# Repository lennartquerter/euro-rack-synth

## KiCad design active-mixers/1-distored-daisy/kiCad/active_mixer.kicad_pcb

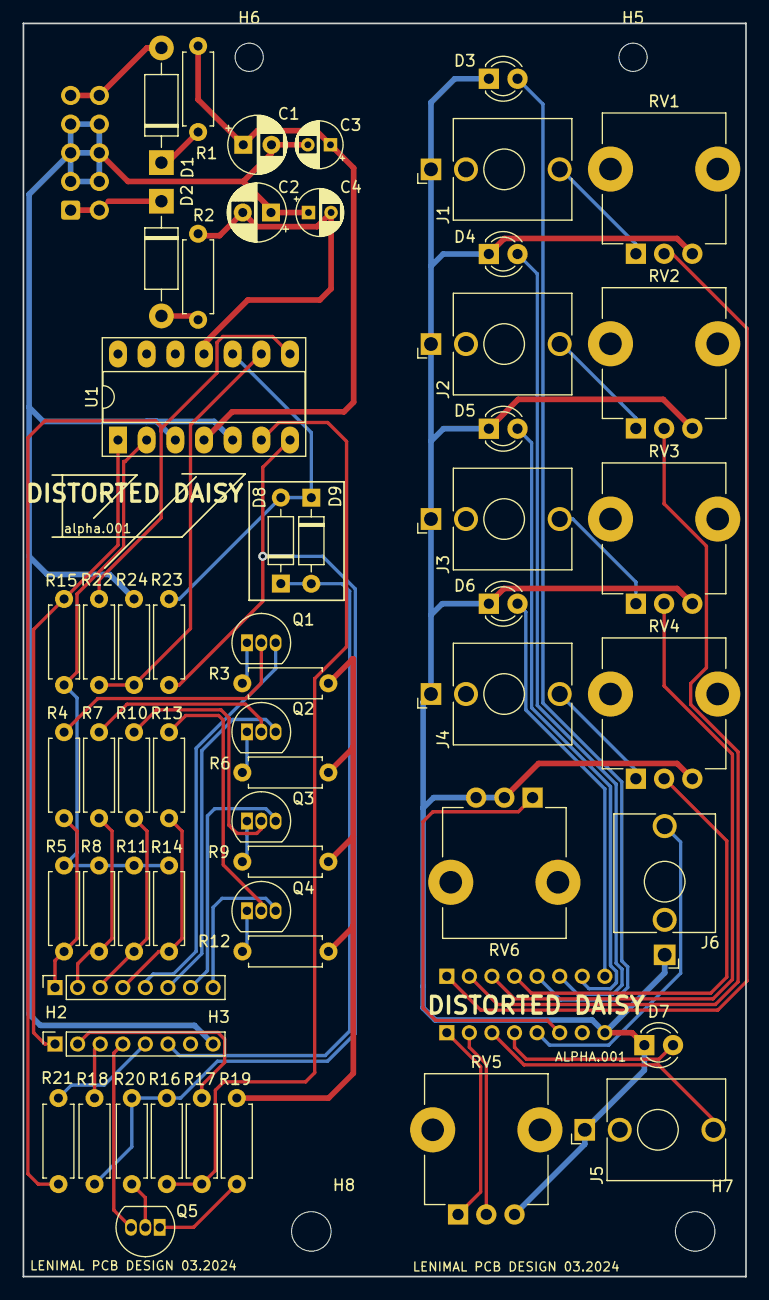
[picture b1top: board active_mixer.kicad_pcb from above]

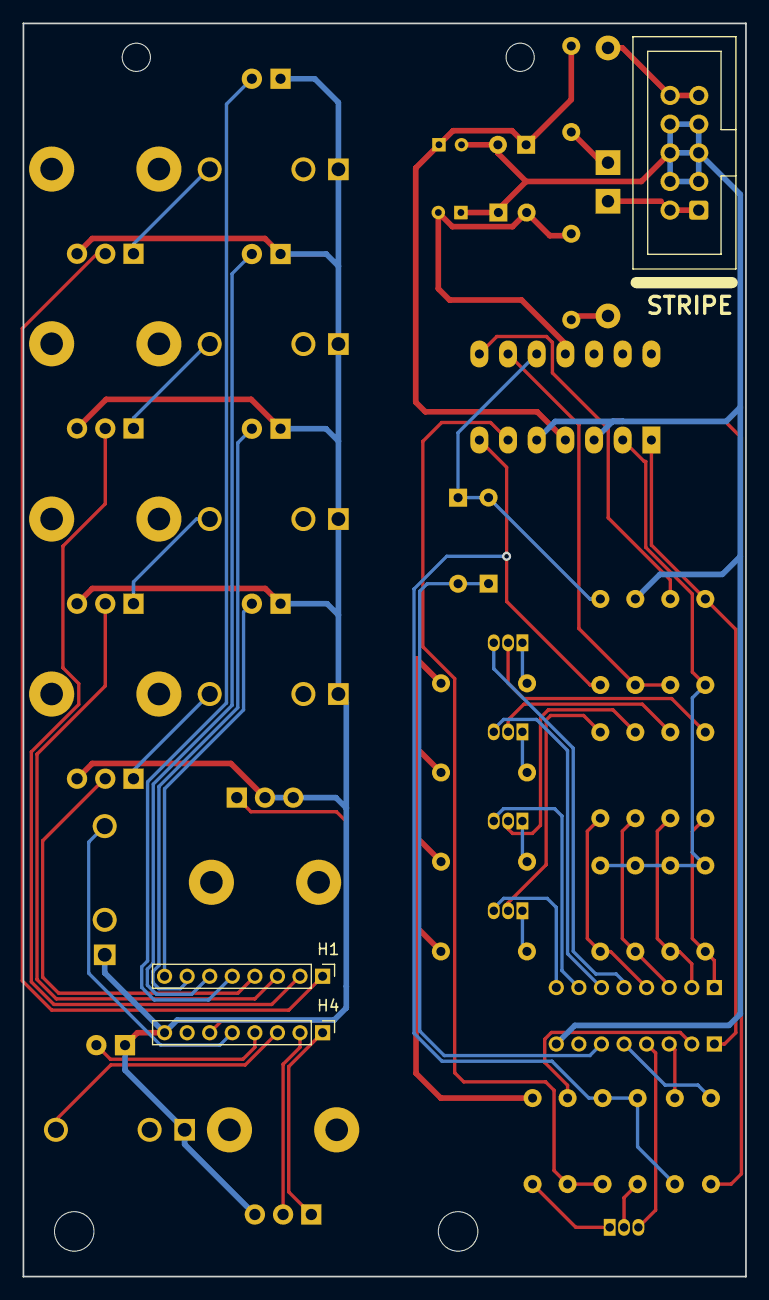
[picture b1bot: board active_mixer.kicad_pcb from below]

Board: 2 copper layers, 64.0 x 111.0 mm, 64 parts (3 on the bottom side), 55 nets.

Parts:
C1, C2: 47uF; CP_Radial_D5.0mm_P2.50mm
C3, C4: 0.1uF; CP_Radial_D4.0mm_P2.00mm
D1, D2: 1N5819; D_DO-41_SOD81_P10.16mm_Horizontal
D3: LED_IN_1; LED_D3.0mm
D4: LED_IN_2; LED_D3.0mm
D5: LED_IN_3; LED_D3.0mm
D6: LED_IN_4; LED_D3.0mm
D7: LED_OUT; LED_D3.0mm
D8, D9: 1N4148; D_DO-35_SOD27_P7.62mm_Horizontal
H1, H4: PinHeader_1x08_P2.00mm_Vertical
H2, H3: PinSocket_1x08_P2.00mm_Vertical
H5, H6: MountingHole; MountingHole_2.5mm
H7, H8: MountingHole; MountingHole_3.5mm
H9: Conn_02x05_PWR_Eurorack; CONN_02x05_PWR
J1: INPUT_1; Jack_3.5mm_QingPu_WQP-PJ398SM_Vertical_CircularHoles
J2: INPUT_2; Jack_3.5mm_QingPu_WQP-PJ398SM_Vertical_CircularHoles
J3: INPUT_3; Jack_3.5mm_QingPu_WQP-PJ398SM_Vertical_CircularHoles
J4: INPUT_4; Jack_3.5mm_QingPu_WQP-PJ398SM_Vertical_CircularHoles
J5, J6: OUTPUT; Jack_3.5mm_QingPu_WQP-PJ398SM_Vertical_CircularHoles
Q1, Q2, Q3, Q4, Q5: BC547; TO-92_Inline
R1, R2: 10; R_Axial_DIN0207_L6.3mm_D2.5mm_P7.62mm_Horizontal
R3, R6, R9, R12, R18, R19, R21: 1K; R_Axial_DIN0207_L6.3mm_D2.5mm_P7.62mm_Horizontal
R4, R5, R7, R8, R10, R11, R13, R14, R15, R16, R17, R20, R22, R24: 100K; R_Axial_DIN0207_L6.3mm_D2.5mm_P7.62mm_Horizontal
R23: 27K; R_Axial_DIN0207_L6.3mm_D2.5mm_P7.62mm_Horizontal
RV1, RV2, RV3, RV4, RV5: B100K; Potentiometer_TT_P0915N
RV6: B20K; Potentiometer_TT_P0915N
U1: TL074; DIP-14_W7.62mm_Socket_LongPads

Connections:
+12V: C1.1, C3.1, R1.2, R3.1, R6.1, R9.1, R12.1, R19.1, U1.4 (V+)
-12V: C2.2, C4.2, R2.2, U1.11 (V-)
GNDREF: C1.2, C2.1, C3.2, C4.1, D3.1 (K), D4.1 (K), D5.1 (K), D6.1 (K), D7.1 (K), H3.8, H4.8, H9.3, H9.4, H9.5, H9.6, H9.7, H9.8, J1.S, J2.S, J3.S, J4.S, J5.S, J6.S, R23.1, RV1.3, RV2.3, RV3.3, RV4.3, RV5.3, RV6.2, RV6.3, U1.3 (+), U1.5 (+)
unnamed: D1.2 (A), H9.9, H9.10
unnamed: D1.1 (K), R1.1
unnamed: D2.2 (A), R2.1
unnamed: D2.1 (K), H9.1, H9.2
unnamed: D3.2 (A), H1.5
unnamed: D4.2 (A), H1.6
unnamed: D5.2 (A), H1.7
unnamed: D6.2 (A), H1.8
unnamed: D7.2 (A), H4.4
unnamed: D8.2 (A), D9.1 (K), R24.2, U1.10 (+)
unnamed: D8.1 (K), D9.2 (A), H3.6
unnamed: H1.1, RV1.2
unnamed: H1.2, RV2.2
unnamed: H1.3, RV3.2
unnamed: H1.4, RV4.2
unnamed: H2.1, R4.1, R5.1
unnamed: H2.2, R7.1, R8.1
unnamed: H2.3, R10.1, R11.1
unnamed: H2.4, R13.1, R14.1
unnamed: H3.1, R15.2, U1.1
unnamed: H3.2, R17.1
unnamed: H3.3, R18.2
unnamed: H3.5, R21.2
unnamed: H4.1, RV5.1
unnamed: H4.2, RV5.2
unnamed: H4.3, J5.T
unnamed: H4.5, J6.T
unnamed: H4.6, RV6.1
unnamed: J1.T, RV1.1
unnamed: J2.T, RV2.1
unnamed: J3.T, RV3.1
unnamed: J4.T, RV4.1
unnamed: Q1.2 (B), R4.2
unnamed: Q1.1 (C), R3.2
unnamed: H2.5, Q1.3 (E)
unnamed: Q2.2 (B), R7.2
unnamed: Q2.1 (C), R6.2
unnamed: H2.6, Q2.3 (E)
unnamed: Q3.2 (B), R10.2
unnamed: Q3.1 (C), R9.2
unnamed: H2.7, Q3.3 (E)
unnamed: Q4.2 (B), R13.2
unnamed: Q4.1 (C), R12.2
unnamed: H2.8, Q4.3 (E)
unnamed: Q5.2 (B), R20.2
unnamed: Q5.1 (C), R19.2
unnamed: H3.4, Q5.3 (E)
unnamed: R16.2, R18.1, R20.1, R24.1, U1.7
unnamed: R21.1, R22.2, U1.8
unnamed: R5.2, R8.2, R11.2, R14.2, R15.1, U1.2 (-)
unnamed: R16.1, R17.2, U1.6 (-)
unnamed: R22.1, R23.2, U1.9 (-)

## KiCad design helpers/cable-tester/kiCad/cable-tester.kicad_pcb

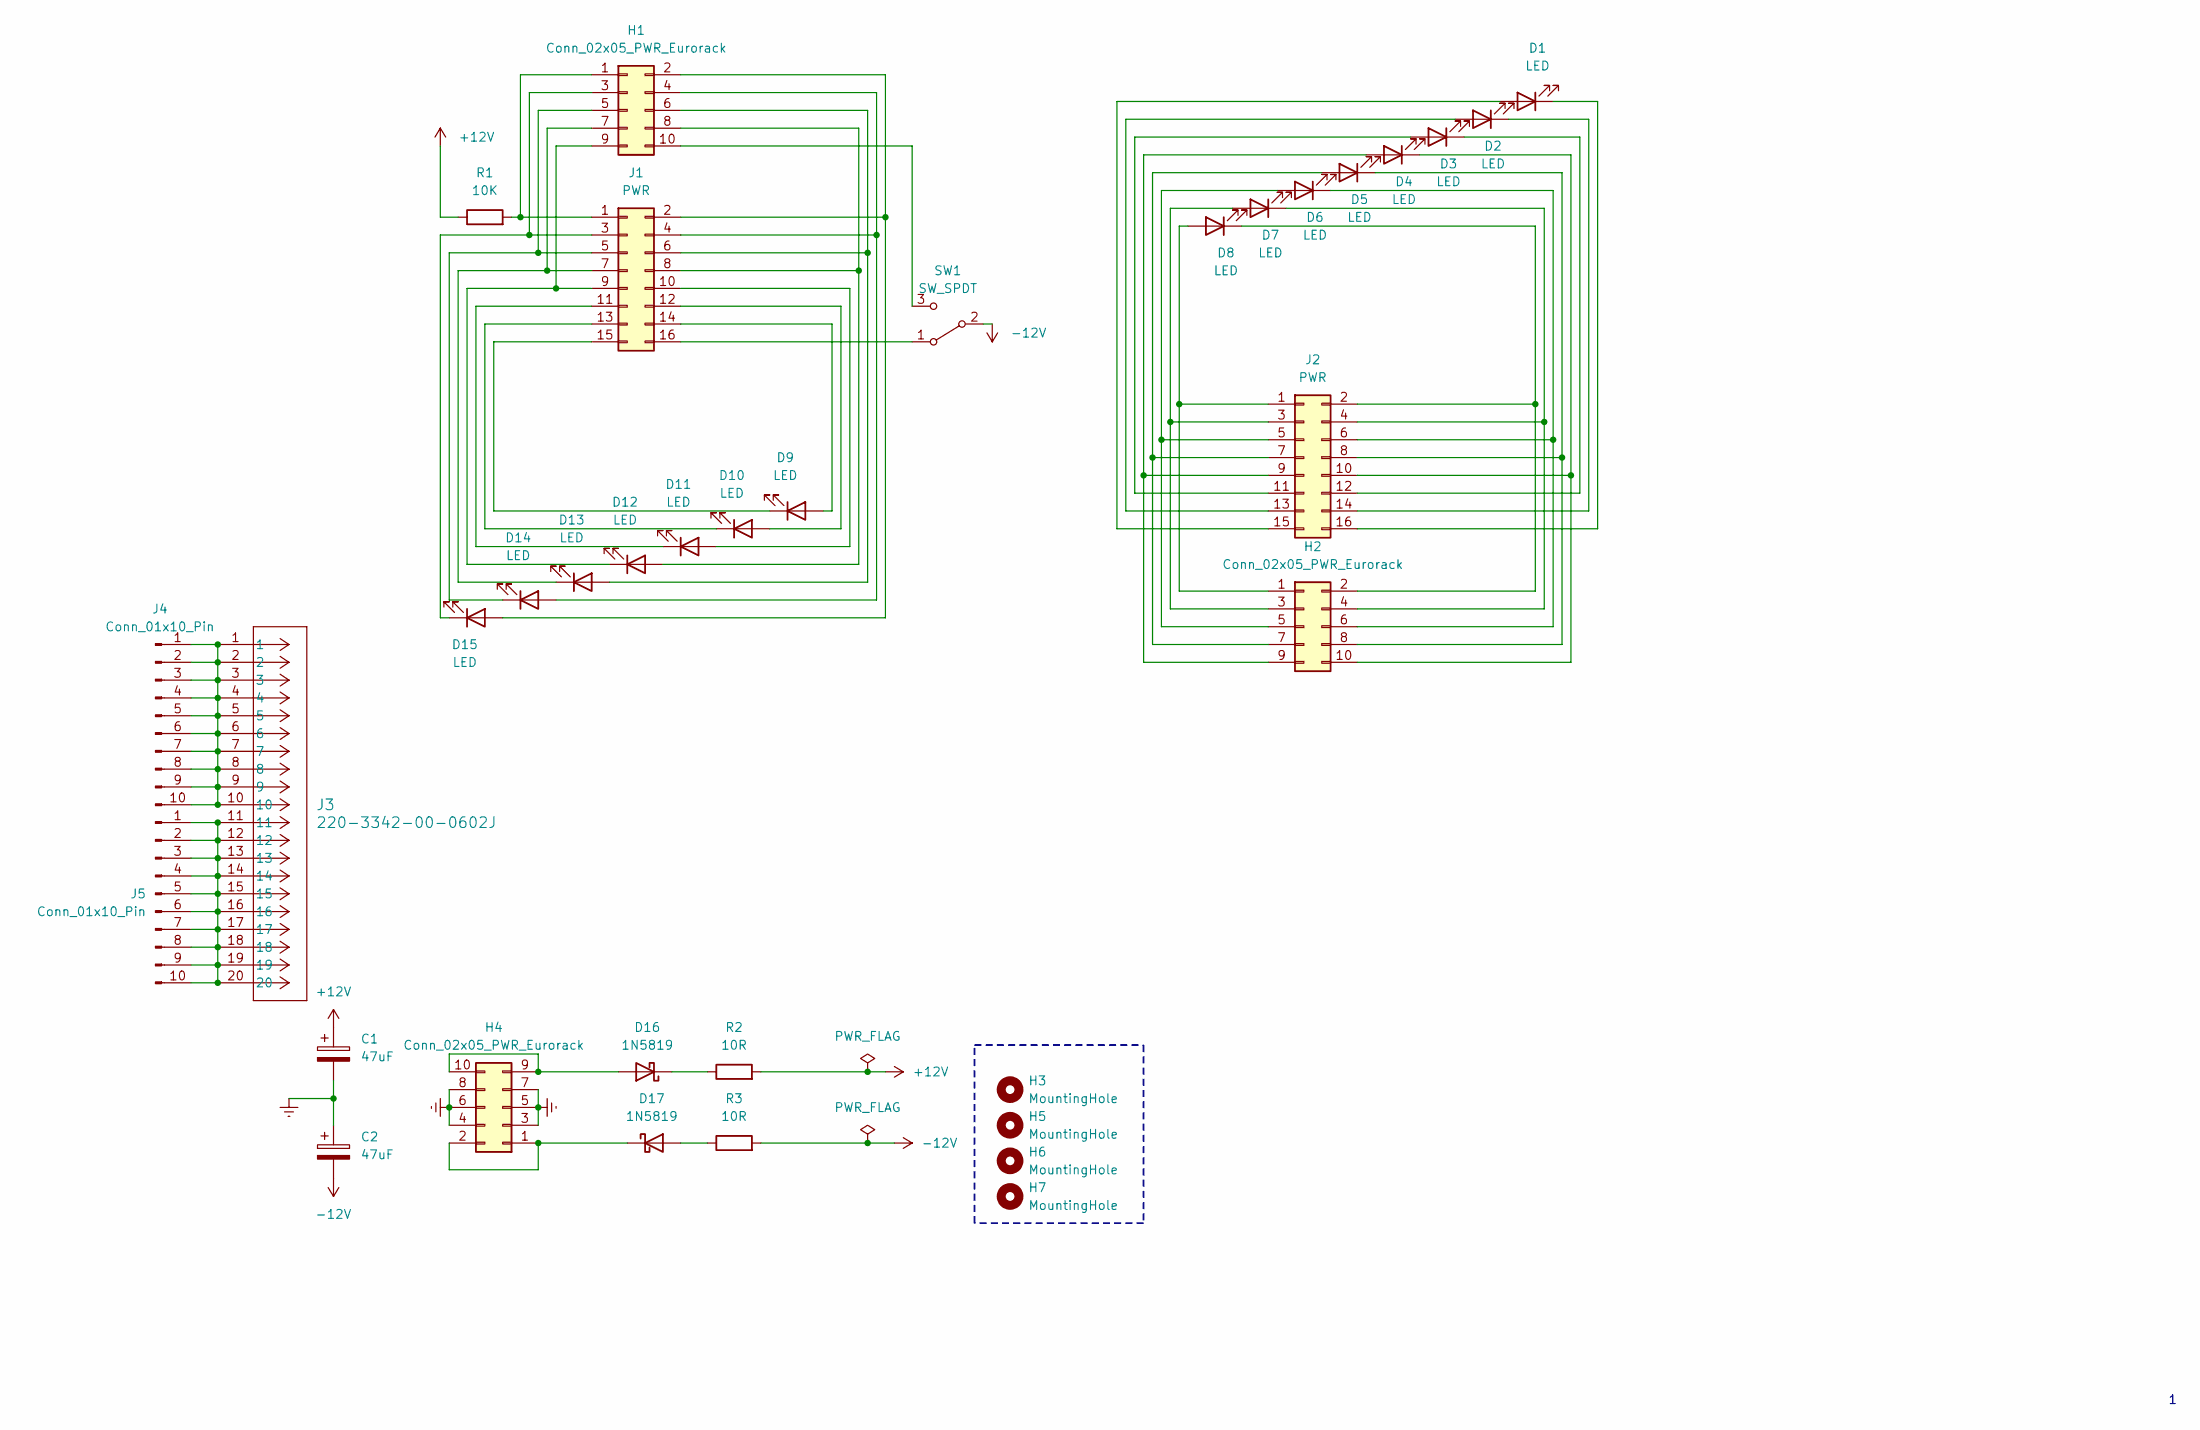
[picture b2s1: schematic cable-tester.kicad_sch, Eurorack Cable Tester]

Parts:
C1, C2: 47uF; CP_Radial_D6.3mm_P2.50mm
D1, D2, D3, D4, D5, D6, D7, D8, D9, D10, D11, D12, D13, D14, D15: LED; LED_D3.0mm
D16, D17: 1N5819; D_SOD-123
H1, H2, H4: Conn_02x05_PWR_Eurorack; IDC-Header_2x05_P2.54mm_Vertical
H3, H5, H6, H7: MountingHole; MountingHole_3.2mm_M3
J1, J2: PWR; IDC-Header_2x08_P2.54mm_Vertical
J3: 220-3342-00-0602J; DIP_tester_20pos
J4, J5: Conn_01x10_Pin; PinHeader_1x10_P2.54mm_Vertical
R1: 10K; R_0805_2012Metric_Pad1.20x1.40mm_HandSolder
R2, R3: 10R; R_0805_2012Metric_Pad1.20x1.40mm_HandSolder
SW1: SW_SPDT; SW_default

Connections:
+12V: C1.1, R1.1, R2.2
-12V: C2.2, R3.2, SW1.2 (B)
GNDREF: C1.2, C2.1, H4.3, H4.4, H4.5, H4.6, H4.7, H4.8
unnamed: D1.2 (A), J2.15 (GATE)
unnamed: D1.1 (K), J2.16 (GATE)
unnamed: D2.2 (A), J2.13 (CV)
unnamed: D2.1 (K), J2.14 (CV)
unnamed: D3.2 (A), J2.11 (+5V)
unnamed: D3.1 (K), J2.12 (+5V)
unnamed: D4.2 (A), H2.9, J2.9 (+12V)
unnamed: D4.1 (K), H2.10, J2.10 (+12V)
unnamed: D5.2 (A), H2.7, J2.7 (GND)
unnamed: D5.1 (K), H2.8, J2.8 (GND)
unnamed: D6.2 (A), H2.5, J2.5 (GND)
unnamed: D6.1 (K), H2.6, J2.6 (GND)
unnamed: D7.2 (A), H2.3, J2.3 (GND)
unnamed: D7.1 (K), H2.4, J2.4 (GND)
unnamed: D8.2 (A), H2.1, J2.1 (-12V)
unnamed: D8.1 (K), H2.2, J2.2 (-12V)
unnamed: D9.2 (A), J1.14 (CV)
unnamed: D9.1 (K), J1.15 (GATE)
unnamed: D10.2 (A), J1.12 (+5V)
unnamed: D10.1 (K), J1.13 (CV)
unnamed: D11.2 (A), J1.10 (+12V)
unnamed: D11.1 (K), J1.11 (+5V)
unnamed: D12.2 (A), H1.8, J1.8 (GND)
unnamed: D12.1 (K), H1.9, J1.9 (+12V)
unnamed: D13.2 (A), H1.6, J1.6 (GND)
unnamed: D13.1 (K), H1.7, J1.7 (GND)
unnamed: D14.2 (A), H1.4, J1.4 (GND)
unnamed: D14.1 (K), H1.5, J1.5 (GND)
unnamed: D15.2 (A), H1.2, J1.2 (-12V)
unnamed: D15.1 (K), H1.3, J1.3 (GND)
unnamed: D16.2 (A), H4.9, H4.10
unnamed: D16.1 (K), R2.1
unnamed: D17.2 (A), R3.1
unnamed: D17.1 (K), H4.1, H4.2
unnamed: H1.1, J1.1 (-12V), R1.2
unnamed: H1.10, SW1.3 (C)
unnamed: J3.1, J3.2, J3.3, J3.4, J3.5, J3.6, J3.7, J3.8, J3.9, J3.10, J4.1, J4.2, J4.3, J4.4, J4.5, J4.6, J4.7, J4.8, J4.9, J4.10
unnamed: J3.11, J3.12, J3.13, J3.14, J3.15, J3.16, J3.17, J3.18, J3.19, J3.20, J5.1, J5.2, J5.3, J5.4, J5.5, J5.6, J5.7, J5.8, J5.9, J5.10
unnamed: J1.16 (GATE), SW1.1 (A)

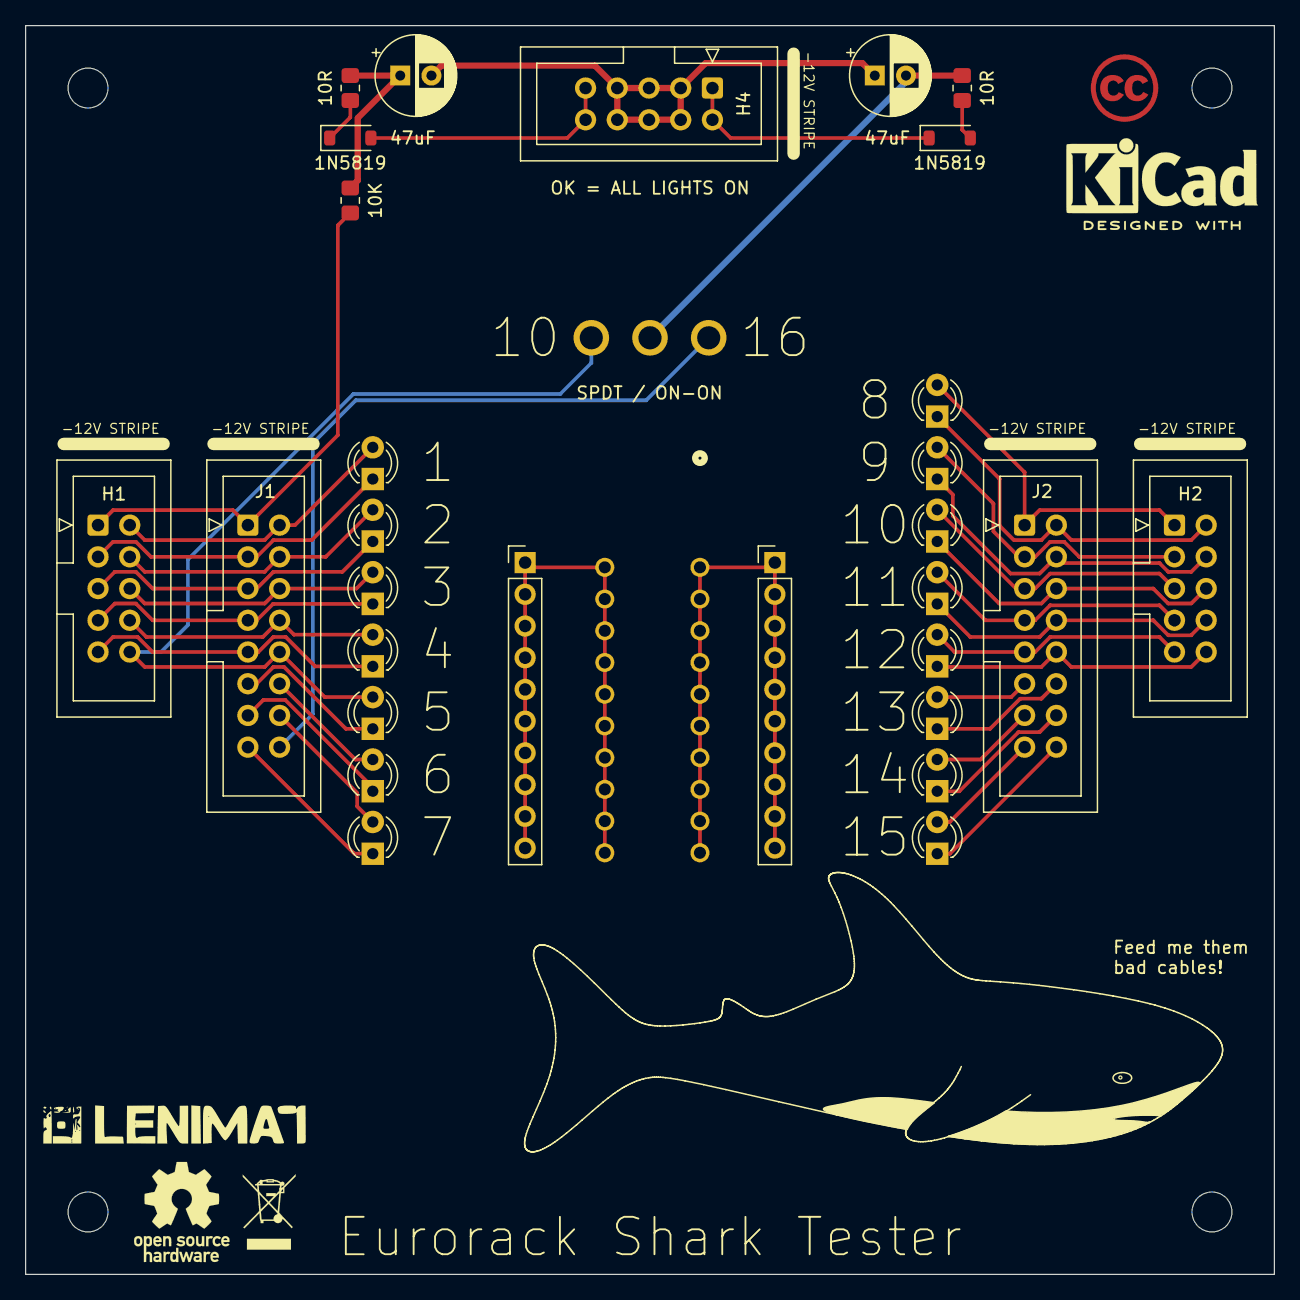
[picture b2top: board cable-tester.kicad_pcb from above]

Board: 2 copper layers, 100.0 x 100.0 mm, 35 parts (0 on the bottom side), 42 nets.

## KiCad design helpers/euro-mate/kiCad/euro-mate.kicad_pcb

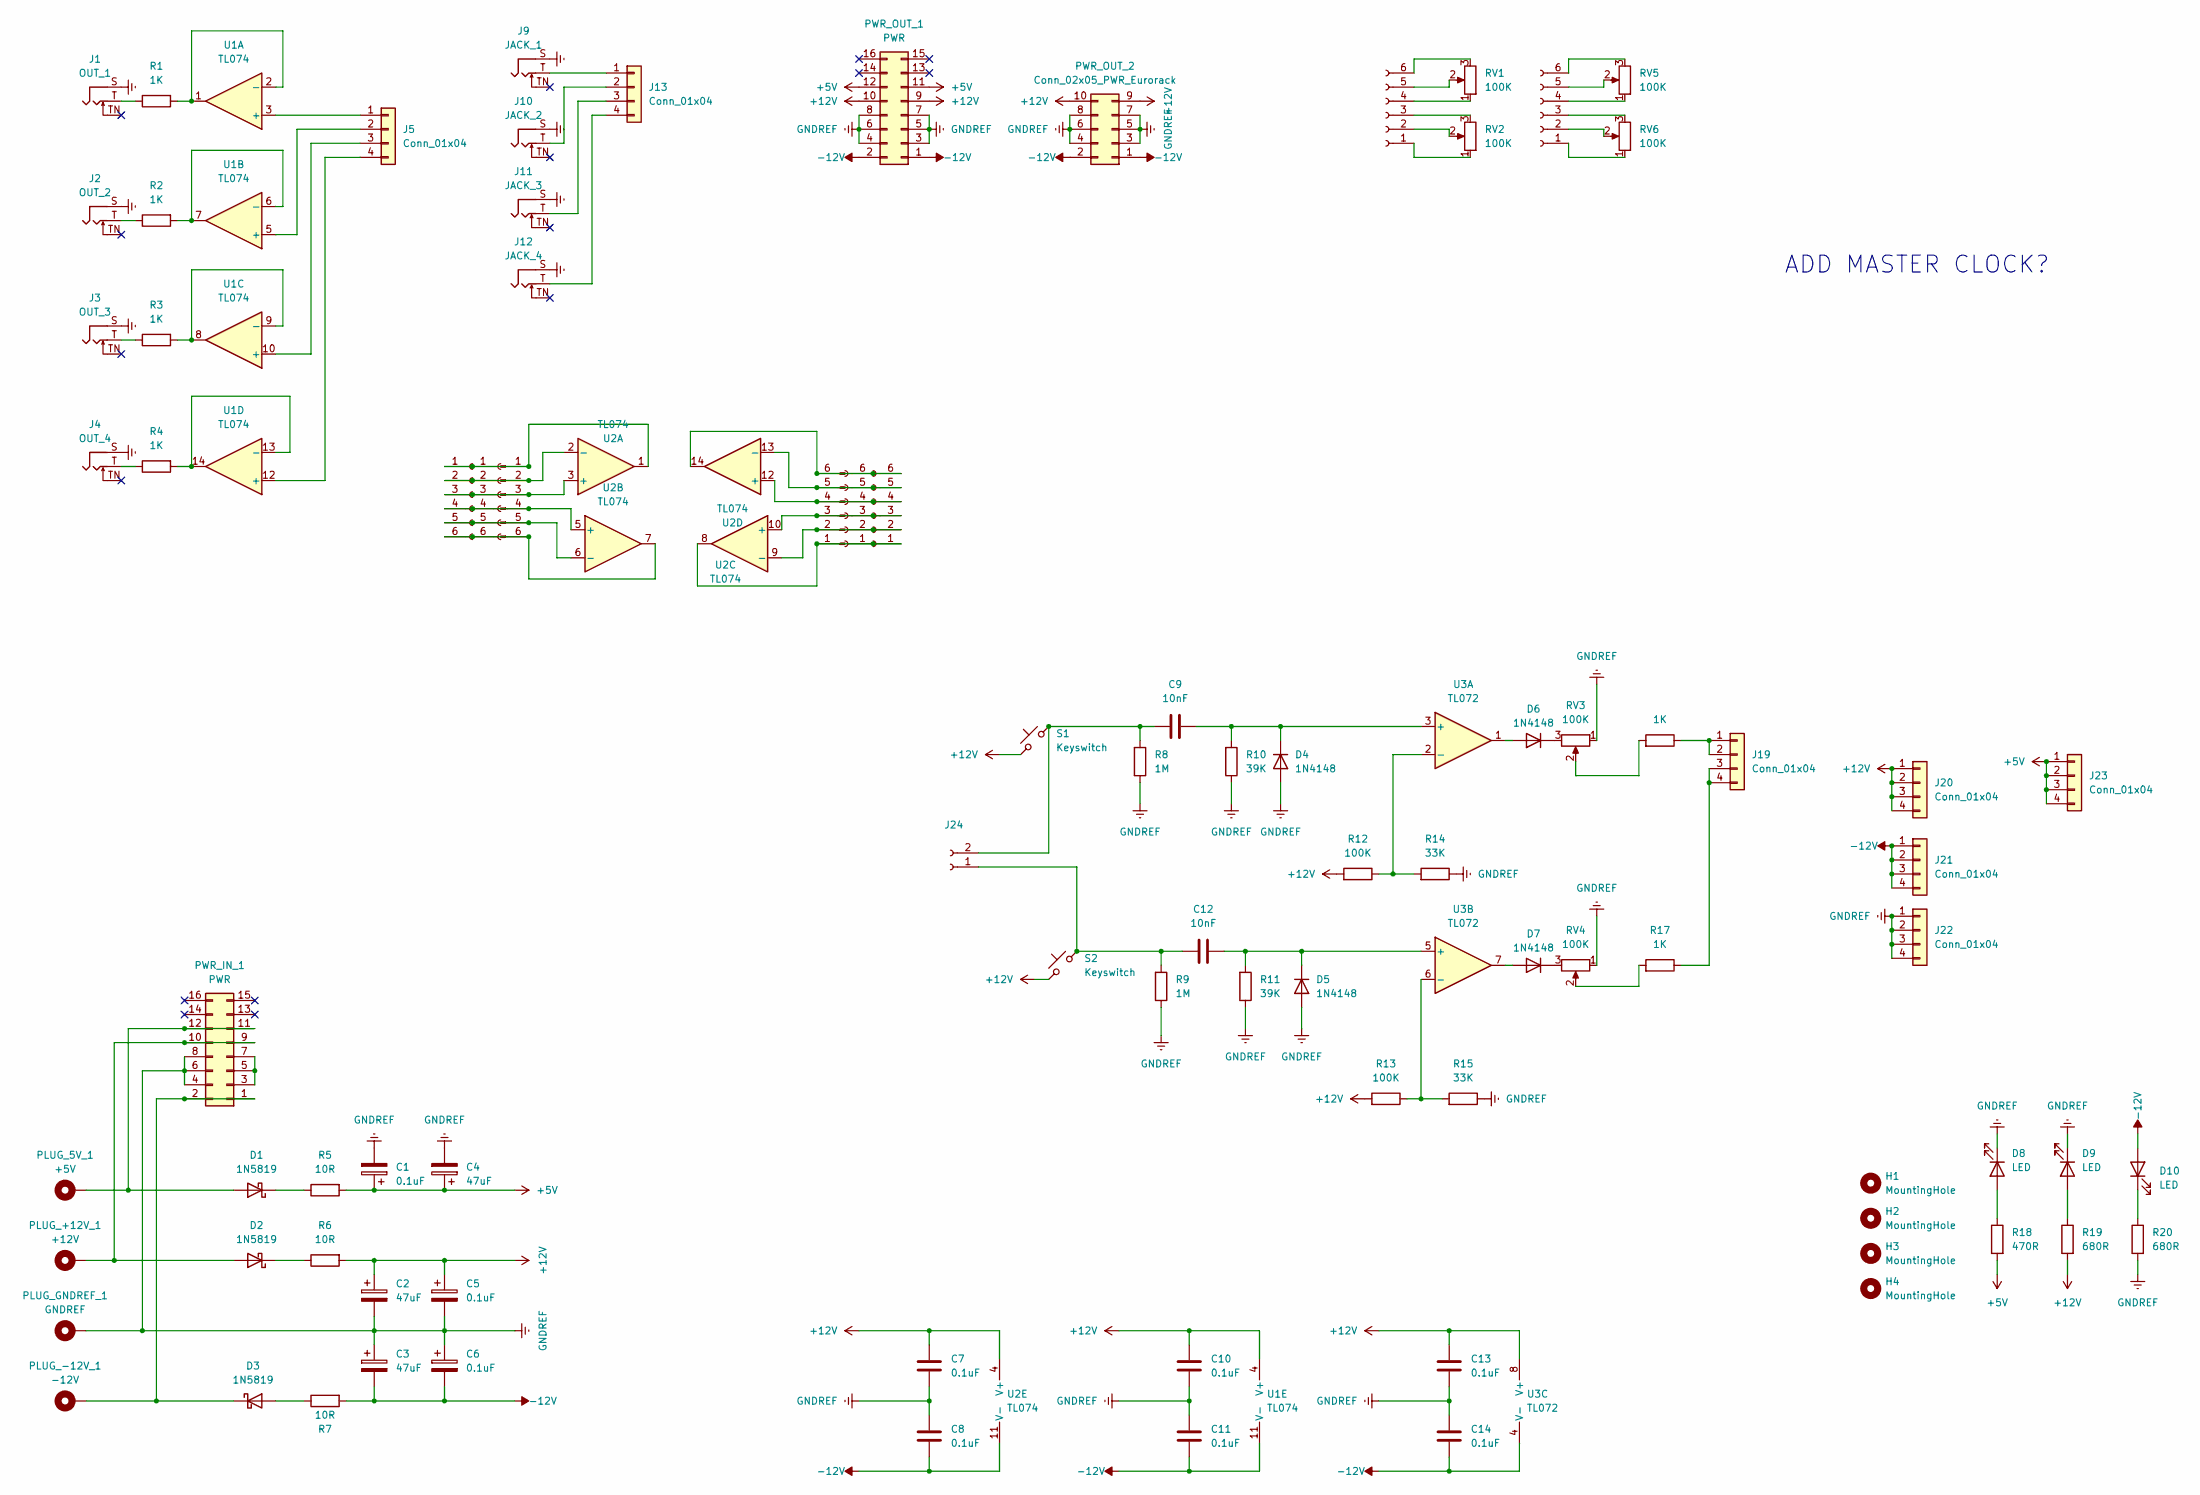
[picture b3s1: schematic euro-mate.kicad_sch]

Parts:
C1, C5, C6: 0.1uF; CP_Radial_D4.0mm_P2.00mm
C2, C3, C4: 47uF; CP_Radial_D6.3mm_P2.50mm
C7, C8, C10, C11, C13, C14: 0.1uF; C_RECT_WIMA_0.1uF
C9, C12: 10nF; C_RECT_WIMA_0.1uF
D1, D2, D3: 1N5819; D_DO-41_SOD81_P10.16mm_Horizontal
D4, D5, D6, D7: 1N4148; D_DO-35_SOD27_P7.62mm_Horizontal
D8, D9, D10: LED; LED_D5.0mm (center Aligned)
H1, H2, H3, H4: MountingHole; MountingHole_3.2mm_M3
J1: OUT_1; Jack_3.5mm_QingPu_WQP-PJ398SM_Vertical_CircularHoles
J2: OUT_2; Jack_3.5mm_QingPu_WQP-PJ398SM_Vertical_CircularHoles
J3: OUT_3; Jack_3.5mm_QingPu_WQP-PJ398SM_Vertical_CircularHoles
J4: OUT_4; Jack_3.5mm_QingPu_WQP-PJ398SM_Vertical_CircularHoles
J5, J13, J19, J20, J21, J22, J23: Conn_01x04; PinSocket_1x04_P2.54mm_Vertical
J6, J8, J15, J16, J17, J18: Conn_01x06_Socket; PinSocket_1x06_P2.54mm_Vertical
J7, J14: Conn_01x06_Pin; PinHeader_1x06_P2.54mm_Vertical
J9: JACK_1; Jack_3.5mm_QingPu_WQP-PJ398SM_Vertical_CircularHoles
J10: JACK_2; Jack_3.5mm_QingPu_WQP-PJ398SM_Vertical_CircularHoles
J11: JACK_3; Jack_3.5mm_QingPu_WQP-PJ398SM_Vertical_CircularHoles
J12: JACK_4; Jack_3.5mm_QingPu_WQP-PJ398SM_Vertical_CircularHoles
J24: Conn_01x02_Socket; PinSocket_1x02_P2.54mm_Vertical
PLUG_5V_1: +5V; MountingHole_4.3mm_M4_Pad
PLUG_+12V_1: +12V; MountingHole_4.3mm_M4_Pad
PLUG_-12V_1: -12V; MountingHole_4.3mm_M4_Pad
PLUG_GNDREF_1: GNDREF; MountingHole_4.3mm_M4_Pad
PWR_IN_1: PWR; IDC-Header_2x08_P2.54mm_Vertical
PWR_OUT_1: PWR; IDC-Header_2x08_P2.54mm_Vertical
PWR_OUT_2: Conn_02x05_PWR_Eurorack; IDC-Header_2x05_P2.54mm_Vertical
R1, R2, R3, R4, R16, R17: 1K; R_Default (DIN0207)
R5, R6, R7: 10R; R_Default (DIN0207)
R8, R9: 1M; R_Default (DIN0207)
R10, R11: 39K; R_Default (DIN0207)
R12, R13: 100K; R_Default (DIN0207)
R14, R15: 33K; R_Default (DIN0207)
R18: 470R; R_Default (DIN0207)
R19, R20: 680R; R_Default (DIN0207)
RV1, RV2, RV3, RV4, RV5, RV6: 100K; Potentiometer_TT_P0915N
S1, S2: Keyswitch; SW_Cherry_MX_PCB_1.00u
U1, U2: TL074; DIP-14_W7.62mm_Socket_LongPads
U3: TL072; DIP-8_W7.62mm_Socket_LongPads

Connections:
+5V: C1.1, C4.1, J23.1, J23.2, J23.3, J23.4, PWR_OUT_1.11 (+5V), PWR_OUT_1.12 (+5V), R5.1, R18.1
+12V: C2.1, C5.1, C7.1, C10.1, C13.1, J20.1, J20.2, J20.3, J20.4, PWR_OUT_1.9 (+12V), PWR_OUT_1.10 (+12V), PWR_OUT_2.9, PWR_OUT_2.10, R6.1, R12.1, R13.1, R19.1, S1.1, S2.1, U1.4 (V+), U2.4 (V+), U3.8 (V+)
-12V: C3.2, C6.2, C8.2, C11.2, C14.2, D10.2 (A), J21.1, J21.2, J21.3, J21.4, PWR_OUT_1.1 (-12V), PWR_OUT_1.2 (-12V), PWR_OUT_2.1, PWR_OUT_2.2, R7.1, U1.11 (V-), U2.11 (V-), U3.4 (V-)
GNDREF: C1.2, C2.2, C3.1, C4.2, C5.2, C6.1, C7.2, C8.1, C10.2, C11.1, C13.2, C14.1, D4.2 (A), D5.2 (A), D8.1 (K), D9.1 (K), J1.S, J2.S, J3.S, J4.S, J9.S, J10.S, J11.S, J12.S, J22.1, J22.2, J22.3, J22.4, PLUG_GNDREF_1.1, PWR_IN_1.4 (GND), PWR_IN_1.6 (GND), PWR_IN_1.8 (GND), PWR_OUT_1.3 (GND), PWR_OUT_1.4 (GND), PWR_OUT_1.5 (GND), PWR_OUT_1.6 (GND), PWR_OUT_1.7 (GND), PWR_OUT_1.8 (GND), PWR_OUT_2.3, PWR_OUT_2.4, PWR_OUT_2.5, PWR_OUT_2.6, PWR_OUT_2.7, PWR_OUT_2.8, R8.2, R9.2, R10.2, R11.2, R14.2, R15.2, R20.1, RV3.1, RV4.1
unnamed: D1.2 (A), PLUG_5V_1.1, PWR_IN_1.11 (+5V), PWR_IN_1.12 (+5V)
unnamed: D1.1 (K), R5.2
unnamed: D2.2 (A), PLUG_+12V_1.1, PWR_IN_1.9 (+12V), PWR_IN_1.10 (+12V)
unnamed: D2.1 (K), R6.2
unnamed: D3.2 (A), R7.2
unnamed: D3.1 (K), PLUG_-12V_1.1, PWR_IN_1.1 (-12V), PWR_IN_1.2 (-12V)
unnamed: C9.2, D4.1 (K), R10.1, U3.3 (+)
unnamed: C12.2, D5.1 (K), R11.1, U3.5 (+)
unnamed: D6.2 (A), U3.1
unnamed: D6.1 (K), RV3.3
unnamed: D7.2 (A), U3.7
unnamed: D7.1 (K), RV4.3
unnamed: D8.2 (A), R18.2
unnamed: D9.2 (A), R19.2
unnamed: D10.1 (K), R20.2
unnamed: J1.T, R1.2
unnamed: J2.T, R2.2
unnamed: J3.T, R3.2
unnamed: J4.T, R4.2
unnamed: J5.1, U1.3 (+)
unnamed: J5.2, U1.5 (+)
unnamed: J5.3, U1.10 (+)
unnamed: J5.4, U1.12 (+)
unnamed: J6.1, J7.1, J8.1, U2.1
unnamed: J6.2, J7.2, J8.2, U2.2 (-)
unnamed: J6.3, J7.3, J8.3, U2.3 (+)
unnamed: J6.4, J7.4, J8.4, U2.5 (+)
unnamed: J6.5, J7.5, J8.5, U2.6 (-)
unnamed: J6.6, J7.6, J8.6, U2.7
unnamed: J9.T, J13.1
unnamed: J10.T, J13.2
unnamed: J11.T, J13.3
unnamed: J12.T, J13.4
unnamed: J14.1, J15.1, J16.1, U2.8
unnamed: J14.2, J15.2, J16.2, U2.9 (-)
unnamed: J14.3, J15.3, J16.3, U2.10 (+)
unnamed: J14.4, J15.4, J16.4, U2.12 (+)
unnamed: J14.5, J15.5, J16.5, U2.13 (-)
unnamed: J14.6, J15.6, J16.6, U2.14
unnamed: J17.1, RV2.1
unnamed: J17.2, RV2.2
unnamed: J17.3, RV2.3
unnamed: J17.4, RV1.1
unnamed: J17.5, RV1.2
unnamed: J17.6, RV1.3
unnamed: J18.1, RV6.1
unnamed: J18.2, RV6.2
unnamed: J18.3, RV6.3
unnamed: J18.4, RV5.1
unnamed: J18.5, RV5.2
unnamed: J18.6, RV5.3
unnamed: J19.1, J19.2, R16.2
unnamed: J19.3, J19.4, R17.2
unnamed: C12.1, J24.1, R9.1, S2.2
unnamed: C9.1, J24.2, R8.1, S1.2
unnamed: PWR_IN_1.3 (GND), PWR_IN_1.5 (GND), PWR_IN_1.7 (GND)
unnamed: R16.1, RV3.2
unnamed: R17.1, RV4.2
unnamed: R1.1, U1.1, U1.2 (-)
unnamed: R2.1, U1.6 (-), U1.7
unnamed: R3.1, U1.8, U1.9 (-)
unnamed: R4.1, U1.13 (-), U1.14
unnamed: R12.2, R14.1, U3.2 (-)
unnamed: R13.2, R15.1, U3.6 (-)

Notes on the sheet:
ADD MASTER CLOCK?

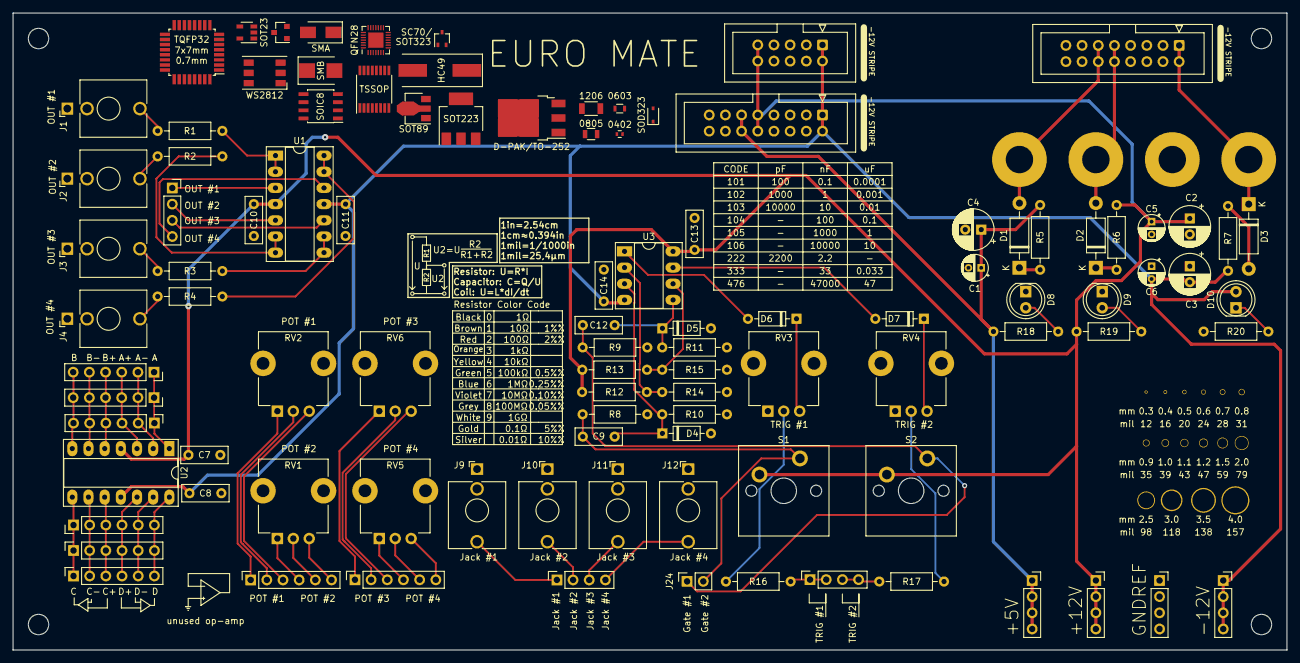
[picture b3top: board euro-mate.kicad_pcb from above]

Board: 2 copper layers, 200.0 x 100.0 mm, 109 parts (0 on the bottom side), 68 nets.

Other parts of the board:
0402: R_0402
0603: R_0603
0805: R_0805
1206: R_1206
D-PAK/TO-252: TO-252-3_TabPin2
HC49: Crystal_SMD_HC49-SD
QFN28: QFN-28-1EP_4x4mm_Pitch0.4mm
SC70/: SOT-323_SC-70
SMA: D_SMA
SMB: D_SMB
SOD323: D_SOD-323
SOIC8: SOIC-8_3.9x4.9mm_Pitch1.27mm
SOT23: SOT-23
SOT23-5: SOT-23-5
SOT89: SOT-89-3
SOT223: SOT-223
TQFP32: TQFP-32_7x7mm_Pitch0.8mm
TSSOP: TSSOP-16_4.4x5mm_Pitch0.65mm
WS2812: LED_WS2812-PLCC6

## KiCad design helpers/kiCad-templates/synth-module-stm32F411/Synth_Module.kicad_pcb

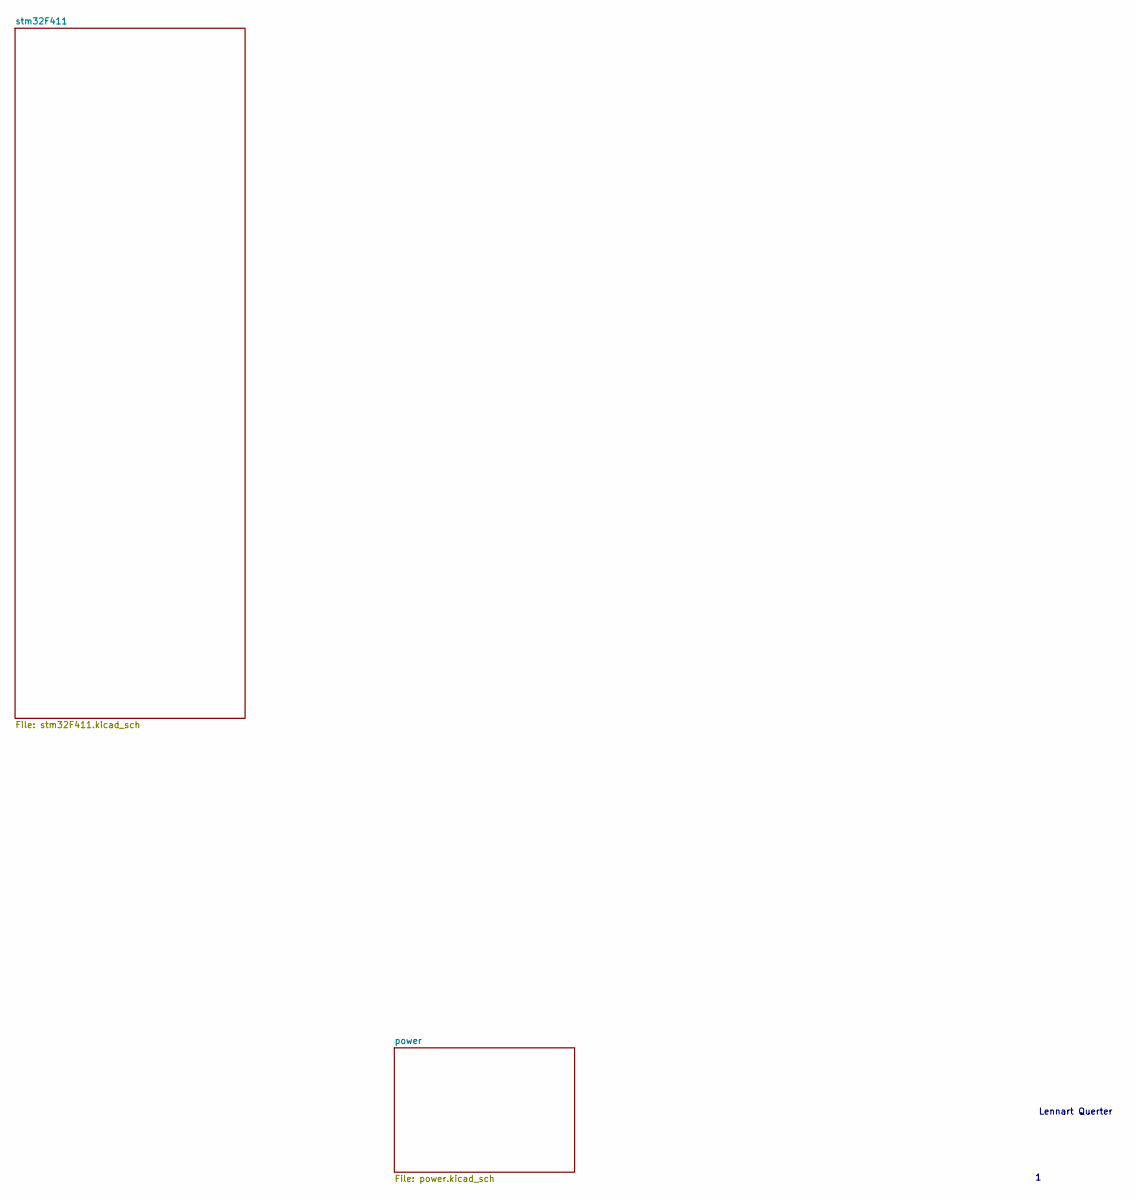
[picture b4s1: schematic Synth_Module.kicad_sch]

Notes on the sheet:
Lennart Querter

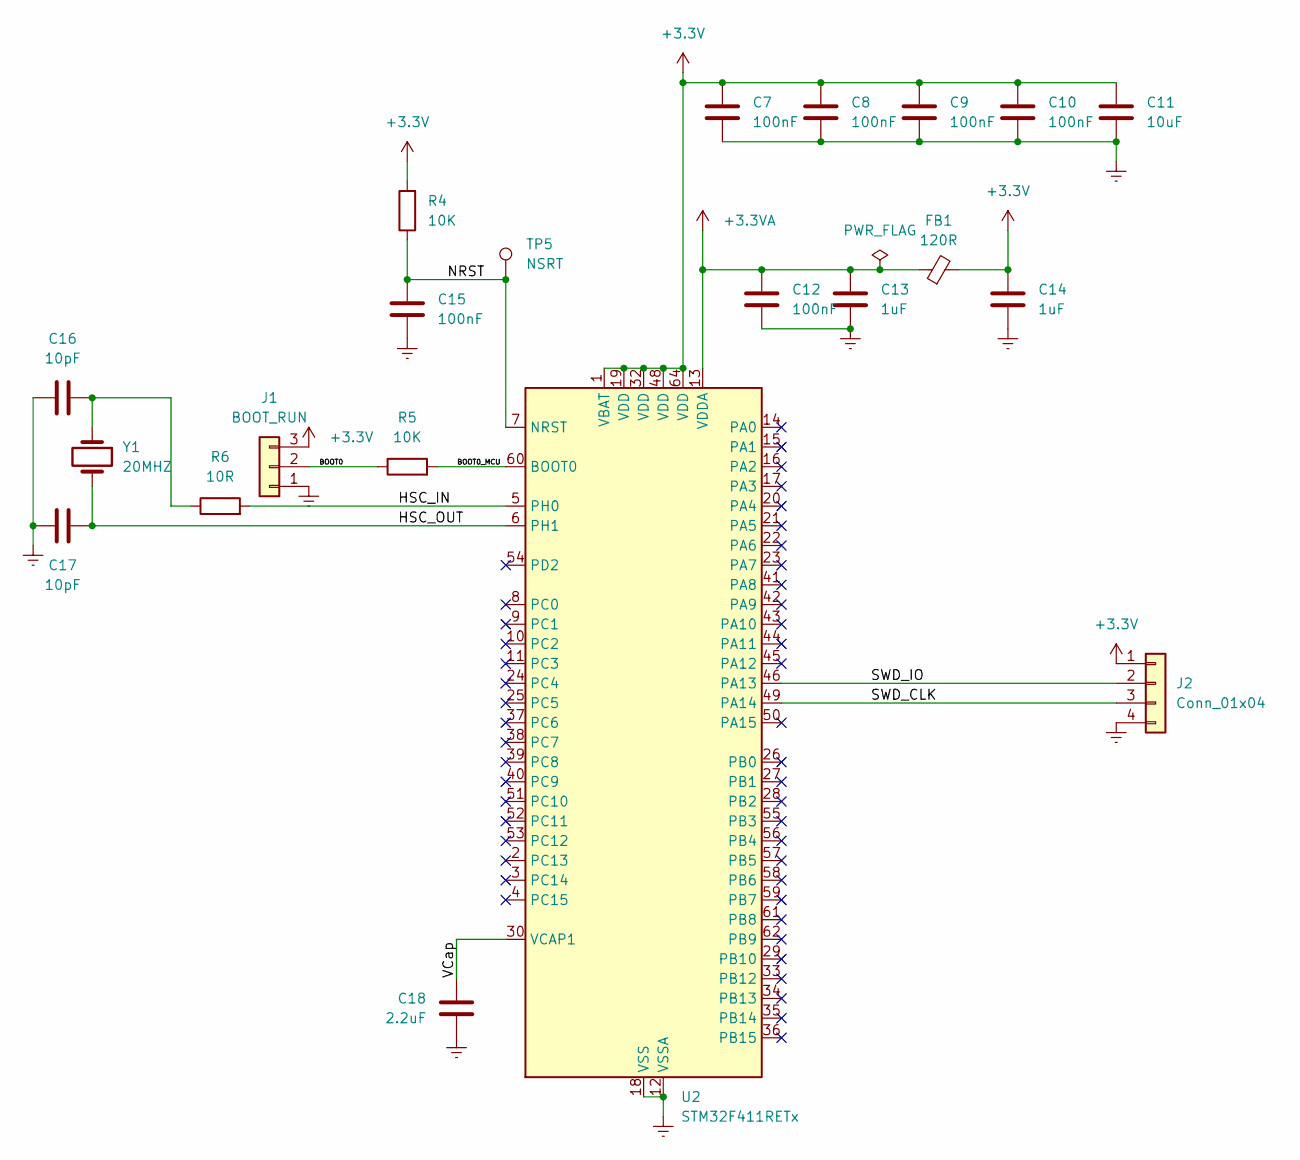
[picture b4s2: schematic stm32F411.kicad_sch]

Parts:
C7, C8, C9, C10, C12, C15: 100nF; C_0805_2012Metric_Pad1.18x1.45mm_HandSolder
C11: 10uF; C_0805_2012Metric_Pad1.18x1.45mm_HandSolder
C13, C14: 1uF; C_0805_2012Metric_Pad1.18x1.45mm_HandSolder
C16, C17: 10pF; C_0805_2012Metric_Pad1.18x1.45mm_HandSolder
C18: 2.2uF; C_0805_2012Metric_Pad1.18x1.45mm_HandSolder
FB1: 120R; L_0805_2012Metric_Pad1.05x1.20mm_HandSolder
J1: BOOT_RUN; PinHeader_1x03_P2.54mm_Vertical
J2: Conn_01x04; PinHeader_1x04_P2.54mm_Vertical
R4, R5: 10K; R_0805_2012Metric_Pad1.20x1.40mm_HandSolder
R6: 10R; R_0805_2012Metric_Pad1.20x1.40mm_HandSolder
TP5: NSRT; Pin_D1.0mm_L10.0mm
U2: STM32F411RETx; LQFP-64_10x10mm_P0.5mm
Y1: 20MHZ; Crystal_SMD_HC49-SD_HandSoldering

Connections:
+3.3V: C7.2, C8.2, C9.2, C10.2, C11.2, C14.2, FB1.2, J1.3, J2.1, R4.2, U2.1 (VBAT), U2.19 (VDD), U2.32 (VDD), U2.48 (VDD), U2.64 (VDD); also elsewhere on the board
+3.3VA: C12.2, C13.2, FB1.1, U2.13 (VDDA)
/stm32F411/BOOT0: J1.2, R5.1
/stm32F411/BOOT0_MCU: R5.2, U2.60 (BOOT0)
/stm32F411/HSC_IN: R6.2, U2.5 (PH0)
/stm32F411/HSC_OUT: C17.1, U2.6 (PH1), Y1.2
/stm32F411/NRST: C15.1, R4.1, TP5.1, U2.7 (NRST)
/stm32F411/SWD_CLK: J2.3, U2.49 (PA14)
/stm32F411/SWD_IO: J2.2, U2.46 (PA13)
/stm32F411/VCap: C18.1, U2.30 (VCAP1)
GNDREF: C7.1, C8.1, C9.1, C10.1, C11.1, C12.1, C13.1, C14.1, C15.2, C16.2, C17.2, C18.2, J1.1, J2.4, U2.12 (VSSA), U2.18 (VSS), U2.31 (VSS), U2.47 (VSS), U2.63 (VSS); also elsewhere on the board
unnamed: C16.1, R6.1, Y1.1

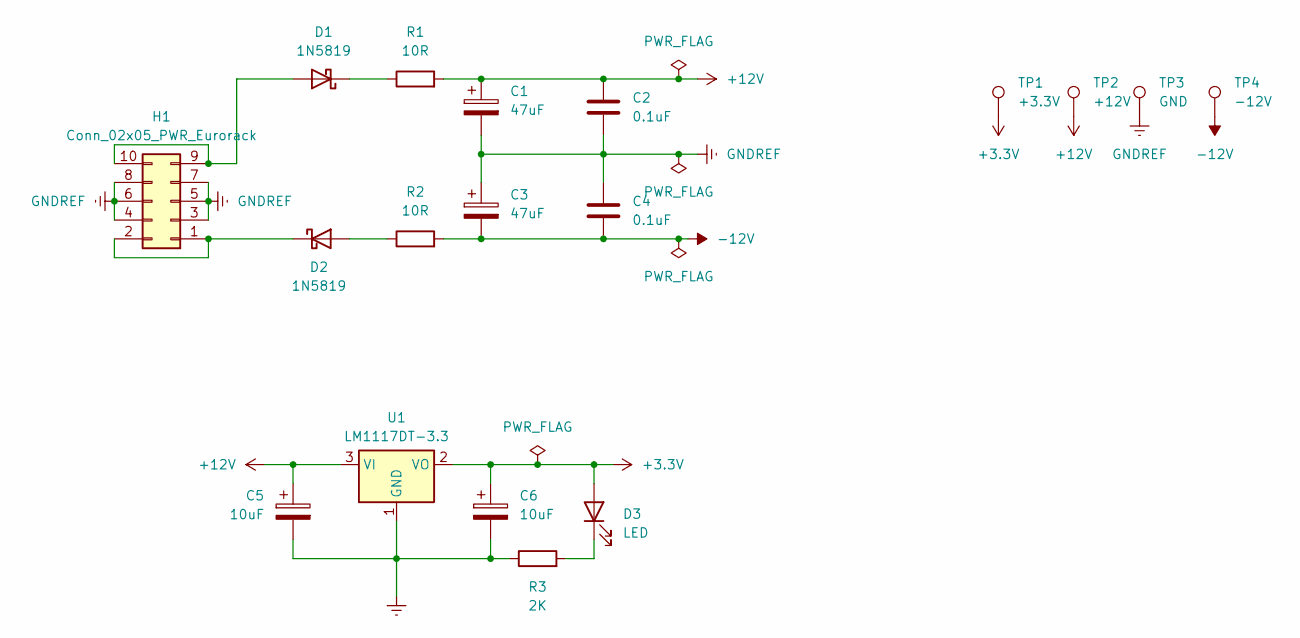
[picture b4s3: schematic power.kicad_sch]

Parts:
C1, C3: 47uF; CP_Radial_D5.0mm_P2.50mm
C2, C4: 0.1uF; C_0805_2012Metric_Pad1.18x1.45mm_HandSolder
C5, C6: 10uF; CP_Radial_D4.0mm_P2.00mm
D1, D2: 1N5819; D_SOD-123
D3: LED; LED_0805_2012Metric_Pad1.15x1.40mm_HandSolder
H1: Conn_02x05_PWR_Eurorack; IDC-Header_2x05_P2.54mm_Vertical
R1, R2: 10R; R_0805_2012Metric_Pad1.20x1.40mm_HandSolder
R3: 2K; R_0805_2012Metric_Pad1.20x1.40mm_HandSolder
TP1: +3.3V; Pin_D1.0mm_L10.0mm
TP2: +12V; Pin_D1.0mm_L10.0mm
TP3: GND; Pin_D1.0mm_L10.0mm
TP4: -12V; Pin_D1.0mm_L10.0mm
U1: LM1117DT-3.3; TO-252-3_TabPin2

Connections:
+3.3V: C6.1, D3.2 (A), TP1.1, U1.2 (VO); also elsewhere on the board
+12V: C1.1, C2.1, C5.1, R1.2, TP2.1, U1.3 (VI)
-12V: C3.2, C4.2, R2.2, TP4.1
GNDREF: C1.2, C2.2, C3.1, C4.1, C5.2, C6.2, H1.3, H1.4, H1.5, H1.6, H1.7, H1.8, R3.1, TP3.1, U1.1 (GND); also elsewhere on the board
unnamed: D1.2 (A), H1.9, H1.10
unnamed: D1.1 (K), R1.1
unnamed: D2.2 (A), R2.1
unnamed: D2.1 (K), H1.1, H1.2
unnamed: D3.1 (K), R3.2
